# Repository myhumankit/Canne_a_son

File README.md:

# Canne à Son — v3

> Canne blanche électronique pour personnes malvoyantes.
> Détecte les obstacles et escaliers via capteurs ultrasons (CH201) et LiDAR (TFMiniPlus), et alerte l'utilisateur par buzzer et vibration.
>
> **Auteur :** BOUFALLOUS Amin — Avril 2026
> **Plateforme :** ESP32-C3 · PlatformIO · Arduino Framework

---

## Matériel

| Composant | Rôle | Interface |
|-----------|------|-----------|
| ESP32-C3 DevKitM-1 | MCU principal | — |
| CH201 × 2 | Ultrasons jusqu'à 4 m | I2C (SDA=6, SCL=7) |
| TFMiniPlus | LiDAR 0–12 m | I2C |
| MPU6050 | IMU (accéléro + gyro) | I2C |
| Buzzer | Alerte sonore | LEDC PWM (GPIO 0) |
| Vibreur | Alerte haptique | LEDC PWM (GPIO 10) |

---

## Démarrage rapide

### Prérequis
- [PlatformIO](https://platformio.org/) installé (CLI ou extension VS Code)

### Build & Flash

```bash
# Compiler
pio run

# Flasher
pio run --target upload

# Moniteur série (9600 baud)
pio device monitor --baud 9600

# Tout en une commande
pio run --target upload && pio device monitor --baud 9600
```

### Sortie série attendue au démarrage

```
╔════════════════════════════════════════╗
║  ✓ CANNE À SON - Architecture V3       ║
║  ✓ Optimisé + Événementiel             ║
╚════════════════════════════════════════╝

[SENSOR] Initializing all sensors...
  ✓ CH201 ready
  ✓ MPU6050 ready (offsets calibrated)
  ✓ LIDAR ready
[PERIPH] Initializing peripherals...
  ✓ Buzzer ready
  ✓ Vibreur ready
[POWER] Initializing power management...
✓ System ready
```

> Si un capteur échoue → 3 bips courts au démarrage + message `❌` sur le port série.
> Si le MPU6050 est absent → la canne reste en mode DETECTING en permanence (sécurité).

---

## Architecture v3

L'architecture repose sur **5 Singletons**, un **bus d'événements** et une **machine d'états**.
Voir [ARCHITECTURE_v3.md](ARCHITECTURE_v3.md) pour le détail complet.

### Flux d'exécution (boucle principale)

```
Timer ISR (100 ms)
    ↓ sensor_ready_flag = true
SensorManager::update()      — lit CH201 × 2, MPU6050, TFMiniPlus
EventManager::postEvent()    — enqueue EVENT_SENSOR_READY
EventManager::processEvents()— dispatch callbacks
AppStateMachine::update()    — logique état courant
PeripheralManager::update()  — gère timeouts buzzer/vibreur
delay(1)
```

### Machine d'états

```
INIT → IDLE ──(mouvement IMU)──→ DETECTING ──(obstacle)──→ ALERT
                ↑                      |                      |
                └──(5s immobile)───────┘                      |
                                  ←──────────(200ms)──────────┘
IDLE ──(2 min sans mouvement)──→ SLEEPING ──(mouvement IMU)──→ DETECTING
```

### Niveaux d'alerte

| Niveau | Distance | Buzzer | Vibration |
|--------|----------|--------|-----------|
| `ALERT_CLOSE` | < 50 cm | 4000 Hz | 255/255 |
| `ALERT_MEDIUM` | 50–100 cm | 2500 Hz | 200/255 |
| `ALERT_FAR` | 100–200 cm | 1500 Hz | 150/255 |

---

## Structure du projet

```
include/
├── types.h              — Tous les enums et structs partagés
├── eventManager.h       — Bus d'événements (singleton, queue x16)
├── sensorManager.h      — Lecture capteurs (singleton)
├── peripheralManager.h  — Buzzer + vibreur (singleton)
├── powerManager.h       — Modes de consommation (singleton)
├── appStateMachine.h    — Machine d'états (singleton)
├── boardConfig.h        — Pins et constantes hardware
└── sensorTemplate.h     — Base template pour nouveaux capteurs

src/
├── main.cpp             — Orchestrateur (~50 lignes)
├── sensorManager.cpp
├── peripheralManager.cpp
├── powerManager.cpp
├── appStateMachine.cpp
├── buzzer.cpp
├── vibreur.cpp
├── CH201.cpp
├── MPU6050_custom.cpp
└── TFMiniPlus.cpp

lib/
├── SmartsonicCH201/     — Driver CH201 (Chirp SonicLib)
└── MPU6050/             — MPU6050_light
```

---

## Règles de développement

- **Jamais de `delay()` dans `loop()`** — tout le timing passe par le flag ISR ou les timeouts de `PeripheralManager`.
- **Types partagés dans `types.h`** — pas d'enums/structs dans les headers individuels.
- **Accès via `::getInstance()`** — jamais d'instanciation directe des managers.
- **Nouveau capteur** → implémenter avec [include/sensorTemplate.h](include/sensorTemplate.h), ajouter un masque dans `SensorManager`, lire dans `update()`.
- **Nouvel événement** → ajouter `event_type_t` dans `types.h`, poster via `postEvent()`, s'abonner via `subscribe()` dans `setup()`.

---

## État du projet

| Feature | État |
|---------|------|
| Détection obstacles CH201 × 2 | ✅ Fonctionnel |
| Alerte buzzer 3 niveaux | ✅ Fonctionnel |
| Alerte vibreur 3 niveaux | ✅ Fonctionnel |
| Détection mouvement IMU | ✅ Fonctionnel |
| Machine d'états IDLE/DETECTING/ALERT/SLEEPING | ✅ Fonctionnel |
| Fallback si IMU absent | ✅ Fonctionnel |
| Signalement erreur capteur (bips) | ✅ Fonctionnel |
| Modes économie énergie (STANDBY/LIGHT_SLEEP) | ✅ Fonctionnel |
| Vrai deep sleep ESP32 | ⚠️ Simulé — wakeup GPIO à implémenter |
| Tests automatisés | ❌ Validation sur hardware uniquement |

---

## Ressources

- [ARCHITECTURE_v3.md](ARCHITECTURE_v3.md) — Conception détaillée et diagrammes
- [QUICK_START.md](QUICK_START.md) — Guide développeur (5 min)
- [include/config_example.h](include/config_example.h) — Exemples de configuration
- [Wikilab My Human Kit](https://wikilab.myhumankit.org/index.php?title=Projets:Canne_a_son_V2) — Documentation projet v2

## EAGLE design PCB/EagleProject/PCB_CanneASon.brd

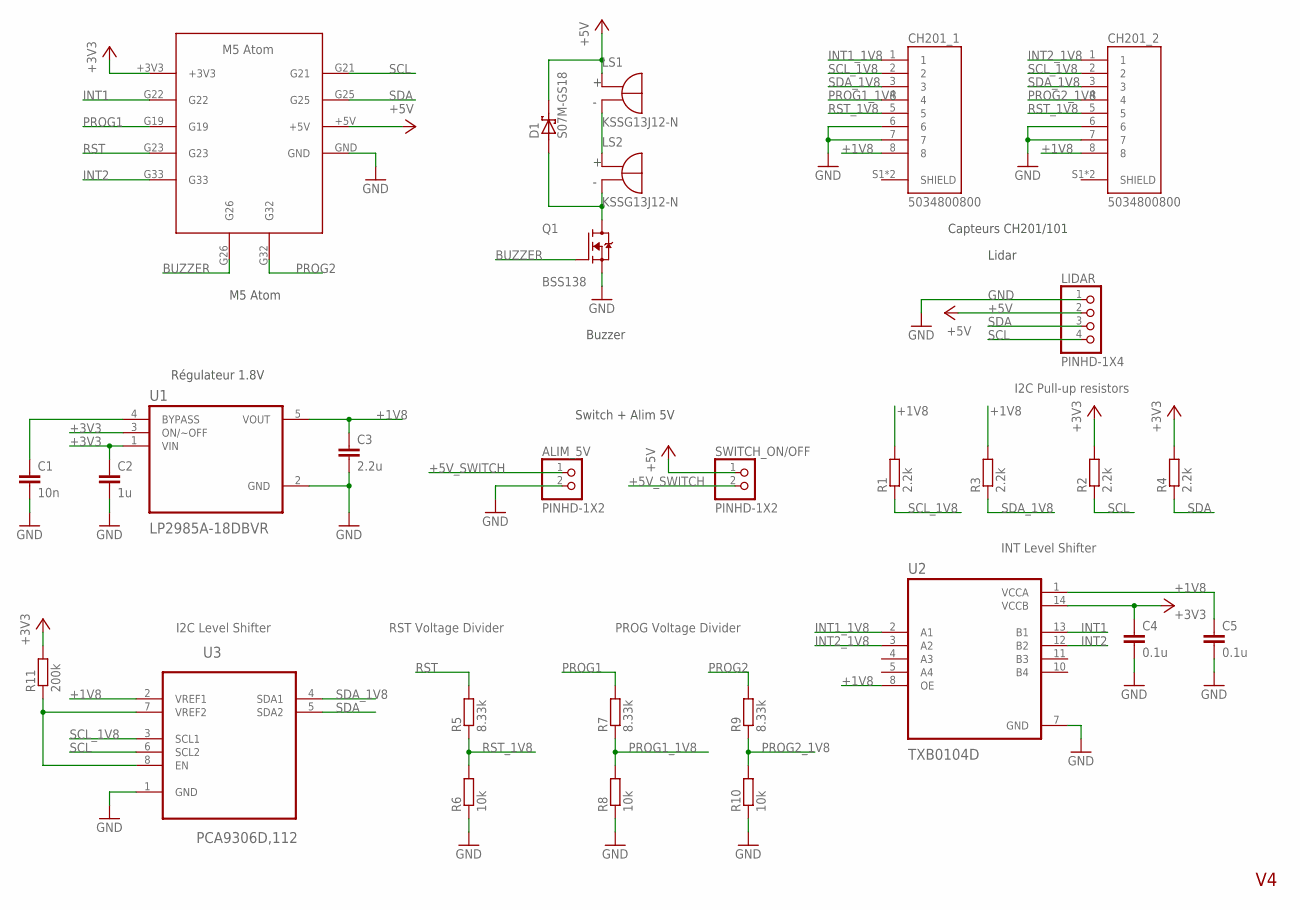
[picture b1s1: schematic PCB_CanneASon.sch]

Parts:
ALIM_5V: PINHD-1X2; 1X02
C1: 10n; C0805
C2: 1u; C0805
C3: 2.2u; C0805
C4, C5: 0.1u; C0805
CH201_1, CH201_2: 5034800800; MOLEX_5034800800
D1: S07M-GS18; DO-219AB
LIDAR: PINHD-1X4; 1X04
LS1, LS2: KSSG13J12-N; XDCR_KSSG13J12-N
Q1: BSS138; SOT95P240X111-3N
R1, R2, R3, R4: 2.2k; R0805
R5, R7, R9: 8.33k; R0805
R6, R8, R10: 10k; R0805
R11: 200k; R0805
SWITCH_ON/OFF: PINHD-1X2; 1X02
U1: LP2985A-18DBVR; SOT95P280X145-5N
U2: TXB0104D; SOIC127P600X175-14N
U3: PCA9306D,112; SOIC127P600X175-8N
U$1: M5ATOM

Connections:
+1V8: C3.1, C5.1, CH201_1.8, CH201_2.8, R1.2, R3.2, U1.5 (VOUT), U2.1 (VCCA), U2.8 (OE), U3.2 (VREF1)
+3V3: C2.1, C4.1, R2.2, R4.2, R11.2, U1.1 (VIN), U1.3 (ON/~OFF), U2.14 (VCCB), U$1.+3V3
+5V: D1.C, LIDAR.2, LS1.P (POS), SWITCH_ON/OFF.1, U$1.+5V
+5V_SWITCH: ALIM_5V.1, SWITCH_ON/OFF.2
BUZZER: Q1.1 (G), U$1.G26
GND: ALIM_5V.2, C1.2, C2.2, C3.2, C4.2, C5.2, CH201_1.6, CH201_1.7, CH201_2.6, CH201_2.7, LIDAR.1, Q1.2 (S), R6.1, R8.1, R10.1, U1.2 (GND), U2.7 (GND), U3.1 (GND), U$1.GND
INT1: U2.13 (B1), U$1.G22
INT1_1V8: CH201_1.1, U2.2 (A1)
INT2: U2.12 (B2), U$1.G33
INT2_1V8: CH201_2.1, U2.3 (A2)
unnamed: C1.1, U1.4 (BYPASS)
unnamed: LS1.N (NEG), LS2.P (POS)
unnamed: D1.A, LS2.N (NEG), Q1.3 (D)
unnamed: R11.1, U3.7 (VREF2), U3.8 (EN)
PROG1: R7.2, U$1.G19
PROG1_1V8: CH201_1.4, R7.1, R8.2
PROG2: R9.2, U$1.G32
PROG2_1V8: CH201_2.4, R9.1, R10.2
RST: R5.2, U$1.G23
RST_1V8: CH201_1.5, CH201_2.5, R5.1, R6.2
SCL: LIDAR.4, R2.1, U3.6 (SCL2), U$1.G21
SCL_1V8: CH201_1.2, CH201_2.2, R1.1, U3.3 (SCL1)
SDA: LIDAR.3, R4.1, U3.5 (SDA2), U$1.G25
SDA_1V8: CH201_1.3, CH201_2.3, R3.1, U3.4 (SDA1)

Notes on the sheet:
Buzzer
Switch + Alim 5V
Lidar
Capteurs CH201/101
M5 Atom
Régulateur 1.8V
I2C Level Shifter
INT Level Shifter
PROG Voltage Divider
I2C Pull-up resistors
RST Voltage Divider

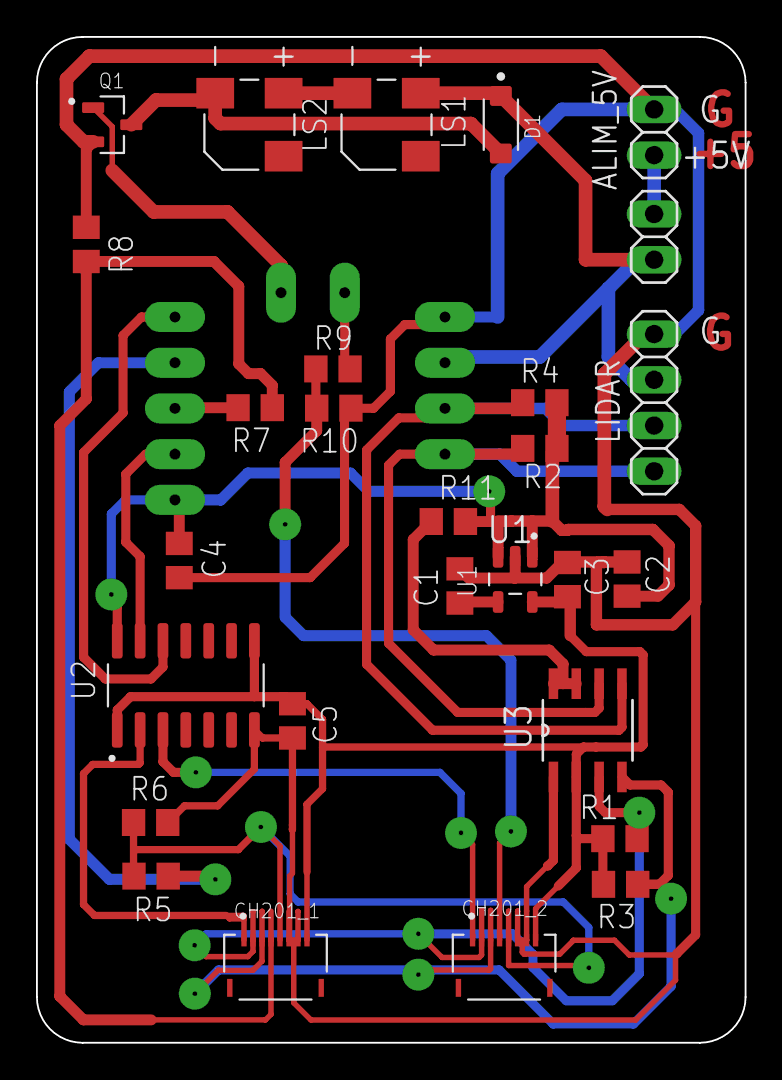
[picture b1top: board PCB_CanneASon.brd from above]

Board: 2 copper layers, 39.4 x 55.9 mm, 29 parts (0 on the bottom side), 24 nets.

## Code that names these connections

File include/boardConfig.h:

/*
 *  Fichier permettant la configuration de la canne
 */

#ifndef PCB_CANNEASON_BOARDCONFIG_H
#define PCB_CANNEASON_BOARDCONFIG_H

/*  Définition de la fréquence du microcontrôleur  */
#define UC_FREQUENCY        100000UL

/*  Paramétrage des capteurs ultrasons CH201  */
#define NB_CH201_SENSOR     2                           // Choix du nombre de capteurs utilisés
#define CH201_FIRMWARE      ch201_gprmt_init            // Firmware des capteurs (ici le mode Multi Thresholds)
#define CH201_MODE          CH_MODE_TRIGGERED_TX_RX     // Mode de capture (CH_MODE_FREERUN ou CH_MODE_TRIGGERED_TX_RX)
#define CH201_MAX_RANGE     4000                        // Distance mesurable maximum en mm
#define CH201_MEASUREMENT_INTERVAL	100	                // Période d'échantillonnage, en ms. Période de 100ms = fréquence d'échantillonnage de 10Hz

/*  Déclaration des Entrées/Sorties  */
#define BUZZER_PIN          0           
#define PIN_RESET           2
#define PIN_SDA             6
#define PIN_SCL             7
#define INT1                4
#define INT2                1
#define PROG1               3
#define PROG2               8
#define VIBREUR_PIN        10
#define switchBuzVibreur1                20
#define switchBuzVibreur2                21 

/*  Paramétrage du retour à l'utiliateur via le buzzer  */
#define NB_BIP              4       // Nombre de cas différents à traiter (ici 4)
#define VOLUME_BIP          127     // Volume des bips
#define BIP_OBSTACLE        2500    // Fréquence bip en cas d'obstacle en Hz
#define BIP_ESCALIER        5000    // Fréquence bip en cas d'escalier/trou en Hz
#define BIP_OBSTACLE_HAUTEUR 800    // Fréquence bip en cas d'obstacle en hauteur en Hz

extern hw_timer_t *My_timer;
#endif //PCB_CANNEASON_BOARDCONFIG_H

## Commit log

2022-09-29 Add 3D Files
2022-09-29 Add PCB Files
    * EAGLE project to make change to the PCB
    * Gerber + Drill files to order the PCB
    * Schematic
2022-09-29 Add PlatformIO project
2022-10-18 Fix high obstacles detection
2023-11-07 add start-up delay for sensor initialisation
2024-10-09 Nouvelle version : Canne à Son V2.1
2026-04-13 fix: corrections architecture v3 + documentation mise à jour
